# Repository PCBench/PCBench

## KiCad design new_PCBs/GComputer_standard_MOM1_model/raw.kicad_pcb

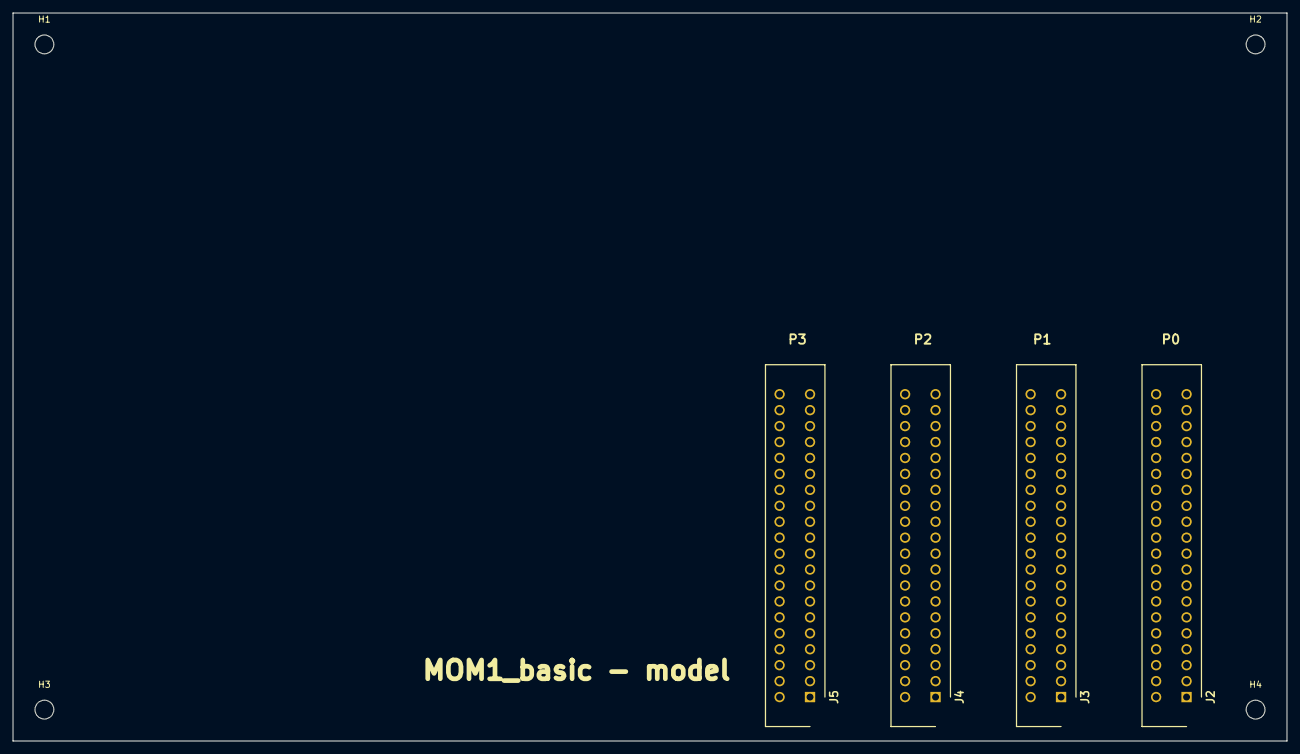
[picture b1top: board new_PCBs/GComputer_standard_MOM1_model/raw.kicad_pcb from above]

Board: 4 copper layers, 203.0 x 116.0 mm, 8 parts (0 on the bottom side), 38 nets, no tracks yet.

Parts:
H1, H2, H3, H4: MountingHole_3mm
J2, J3, J4, J5: PP1_connector_TE_5-5530843-4; TE_5-5530843-4

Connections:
+3V3: J2.39, J3.39, J4.39, J5.39
+5V: J2.40, J3.40, J4.40, J5.40
/BREAD1_0: J2.37, J3.37, J4.37, J5.37
/BREAD1_1: J2.35, J3.35, J4.35, J5.35
/BREAD1_2: J2.33, J3.33, J4.33, J5.33
/BREAD1_3: J2.31, J3.31, J4.31, J5.31
/BREAD1_4: J2.29, J3.29, J4.29, J5.29
/BREAD1_5: J2.27, J3.27, J4.27, J5.27
/BREAD1_6: J2.25, J3.25, J4.25, J5.25
/BREAD1_7: J2.23, J3.23, J4.23, J5.23
/BREAD2_0: J2.21, J3.21, J4.21, J5.21
/BREAD2_1: J2.19, J3.19, J4.19, J5.19
/BREAD2_2: J2.17, J3.17, J4.17, J5.17
/BREAD2_3: J2.15, J3.15, J4.15, J5.15
/BREAD2_4: J2.13, J3.13, J4.13, J5.13
/BREAD2_5: J2.11, J3.11, J4.11, J5.11
/BREAD2_6: J2.9, J3.9, J4.9, J5.9
/BREAD2_7: J2.7, J3.7, J4.7, J5.7
/BWRITE1_0: J2.38, J3.38, J4.38, J5.38
/BWRITE1_1: J2.36, J3.36, J4.36, J5.36
/BWRITE1_2: J2.34, J3.34, J4.34, J5.34
/BWRITE1_3: J2.32, J3.32, J4.32, J5.32
/BWRITE1_4: J2.30, J3.30, J4.30, J5.30
/BWRITE1_5: J2.28, J3.28, J4.28, J5.28
/BWRITE1_6: J2.26, J3.26, J4.26, J5.26
/BWRITE1_7: J2.24, J3.24, J4.24, J5.24
/BWRITE2_0: J2.22, J3.22, J4.22, J5.22
/BWRITE2_1: J2.20, J3.20, J4.20, J5.20
/BWRITE2_2: J2.18, J3.18, J4.18, J5.18
/BWRITE2_3: J2.16, J3.16, J4.16, J5.16
/BWRITE2_4: J2.14, J3.14, J4.14, J5.14
/BWRITE2_5: J2.12, J3.12, J4.12, J5.12
/BWRITE2_6: J2.10, J3.10, J4.10, J5.10
/BWRITE2_7: J2.8, J3.8, J4.8, J5.8
/PERIPHERAL_CLK: J2.3, J3.3, J4.3, J5.3
/SYNC_BIT: J2.6, J3.6, J4.6, J5.6
/~RESET_CLK: J2.5, J3.5, J4.5, J5.5
GND: J2.1, J3.1, J4.1, J5.1

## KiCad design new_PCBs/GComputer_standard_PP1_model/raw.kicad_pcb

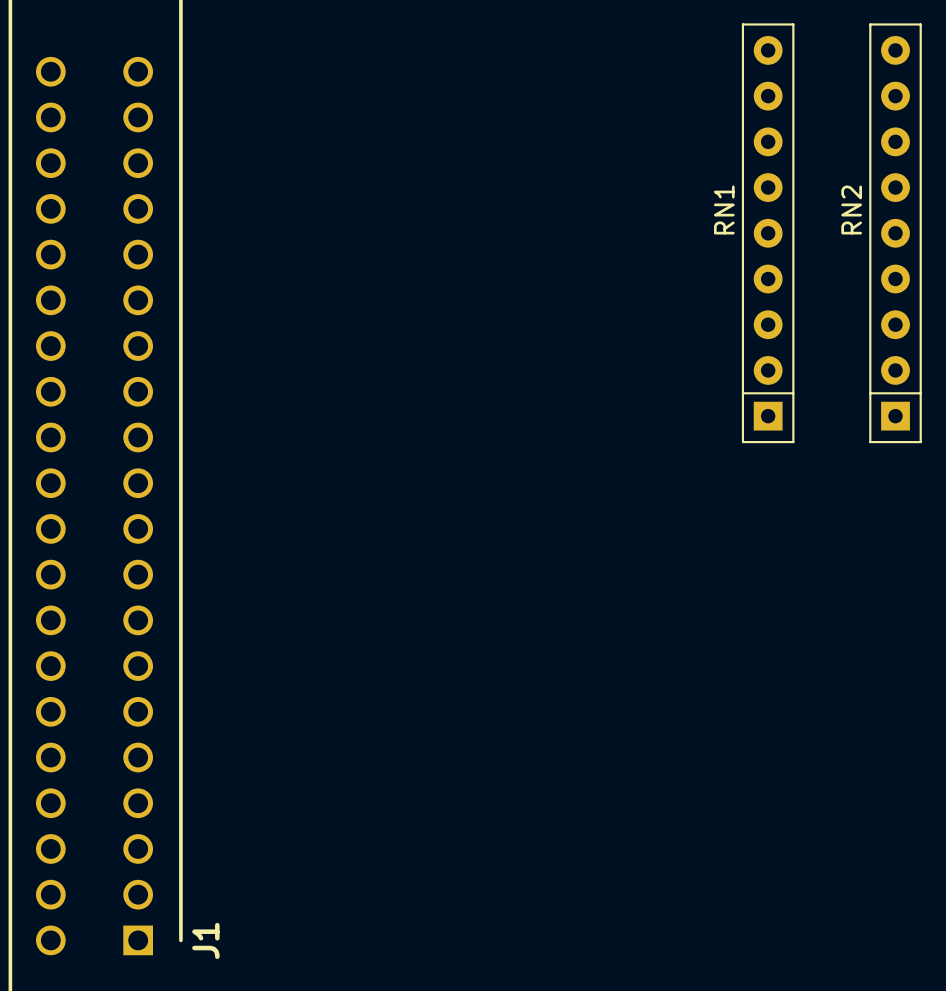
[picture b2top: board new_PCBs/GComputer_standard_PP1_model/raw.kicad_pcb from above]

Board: 4 copper layers, 3 parts (0 on the bottom side), 17 nets, no tracks yet.

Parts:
J1: PP1_receptacle_TE_5-5530843-4; TE_5-5530843-4
RN1, RN2: 8x10k; R_Array_SIP9

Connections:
/BREAD1_0: J1.37, RN1.9
/BREAD1_1: J1.35, RN1.8
/BREAD1_2: J1.33, RN1.7
/BREAD1_3: J1.31, RN1.6
/BREAD1_4: J1.29, RN1.5
/BREAD1_5: J1.27, RN1.4
/BREAD1_6: J1.25, RN1.3
/BREAD1_7: J1.23, RN1.2
/BREAD2_0: J1.21, RN2.9
/BREAD2_1: J1.19, RN2.8
/BREAD2_2: J1.17, RN2.7
/BREAD2_3: J1.15, RN2.6
/BREAD2_4: J1.13, RN2.5
/BREAD2_5: J1.11, RN2.4
/BREAD2_6: J1.9, RN2.3
/BREAD2_7: J1.7, RN2.2
GND: J1.1, RN1.1, RN2.1

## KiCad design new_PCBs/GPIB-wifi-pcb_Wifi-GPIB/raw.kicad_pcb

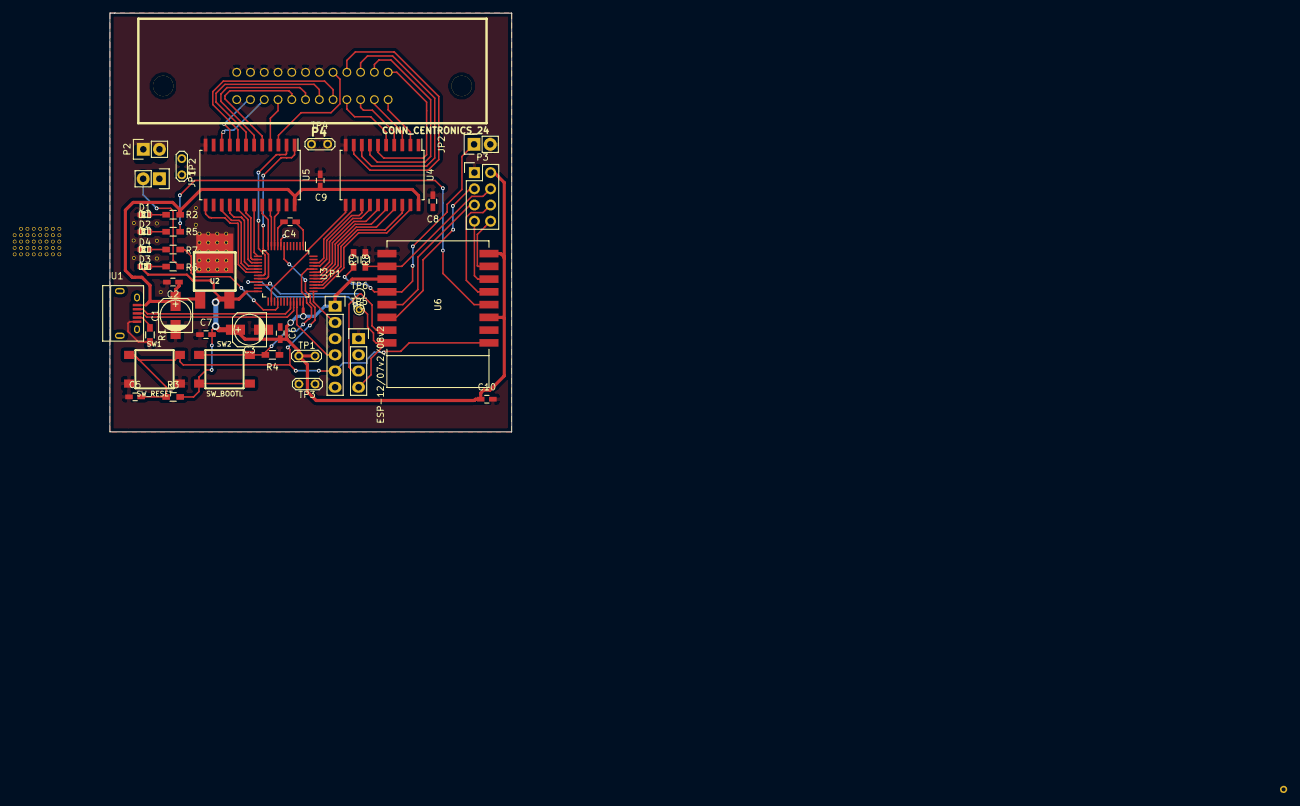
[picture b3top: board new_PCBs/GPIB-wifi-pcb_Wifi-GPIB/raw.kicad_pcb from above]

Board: 2 copper layers, 63.0 x 65.7 mm, 113 parts (0 on the bottom side), 66 nets.

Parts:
C1, C3: 47u; c_elec_5x5.3
C2: 0.33u; C_0603_HandSoldering
C4, C5, C6, C8, C9: 100n; C_0603_HandSoldering
C7: 1u; C_0603_HandSoldering
C10: C; C_0603_HandSoldering
D1: PWR; LED-0603
D2: WIFI; LED-0603
D3: USB; LED-0603
D4: GPIB; LED-0603
GND1, GND2, GND3, GND4, GND5, GND6, GND7, GND8, GND9, GND10, GND11, GND12, GND13, GND14, GND15, GND16, GND17, GND18, GND19, GND20, GND21, GND22, GND23, GND24, GND25, GND26, GND27, GND28, GND29, GND30, GND31, GND32, GND33, GND34, GND35, GND36, GND37, GND38, GND39, GND40, GND41, GND41#2, GND42, GND42#2, GND43, GND43#2, GND44, GND44#2, GND45, GND45#2, GND46, GND46#2, GND47, GND47#2, GND48, GND48#2, GND49, GND50, GND410, GND411, GND412, GND413, GND414, GND415, GND416, GND417, GND418, GND419, GND420: GND; SolderWirePad_single_0-4mmDrill
JP1: USB_LED; Pin_Header_Straight_1x02
JP2: ESP_FLASH_JUMP; Pin_Header_Straight_1x02
P1: SWD; Pin_Header_Straight_1x06
P2: USART; Pin_Header_Straight_1x02
P3: ESP_EXPANSION; Pin_Header_Straight_2x04
P4: CONN_CENTRONICS_24; gpib_conn_male
P5: ESP_PROG; Pin_Header_Straight_1x04
R1: 100k; R_0603_HandSoldering
R2: 270; R_0603_HandSoldering
R3, R4, R5, R6, R7, R8, R9: R; R_0603_HandSoldering
SW1: SW_RESET; SW_PUSH_SMD
SW2: SW_BOOTL; SW_PUSH_SMD
TP1, TP2, TP3, TP4: TESTPOINT
TP5, TP6: TESTPOINT; PINTST
U1: MICRO-B_USB; USB_Micro-B
U2: BA33BC0FP-E2; TO-252
U3: STM32F072CBT6; LQFP-48_7x7mm_Pitch0.5mm
U4: SN75160B; SOIC-20_7.5x12.8mm_Pitch1.27mm
U5: SN75162B; SOIC-24_7.5x15.4mm_Pitch1.27mm
U6: ESP-12/07v2/08v2; ESP-07

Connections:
+3.3V: C3.1, C4.2, C6.2, C7.2, C10.1, D3.1, P1.1, P3.2, P5.2, R3.2, R8.1, SW2.2, TP1.1, U2.3, U3.9, U3.24, U3.36, U3.48, U6.3, U6.8, U6.11
+5V: C1.1, C2.1, C8.1, C9.1, R2.1, TP2.1, U1.1, U2.1, U4.20, U5.24
/GPIB and Cortex M0/ATN: U3.16, U5.16
/GPIB and Cortex M0/D1: U3.38, U4.19
/GPIB and Cortex M0/D2: U3.39, U4.18
/GPIB and Cortex M0/D3: U3.40, U4.17
/GPIB and Cortex M0/D4: U3.41, U4.16
/GPIB and Cortex M0/D5: U3.42, U4.15
/GPIB and Cortex M0/D6: U3.43, U4.14
/GPIB and Cortex M0/D7: U3.45, U4.13
/GPIB and Cortex M0/D8: U3.46, U4.12
/GPIB and Cortex M0/DAV: U3.14, U5.18
/GPIB and Cortex M0/EOI: U3.15, U5.17
/GPIB and Cortex M0/ESP_GPIO_4: P3.3, U6.14
/GPIB and Cortex M0/ESP_GPIO_5: P3.5, U6.13
/GPIB and Cortex M0/ESP_GPIO_12: P3.7, U6.6
/GPIB and Cortex M0/ESP_GPIO_13: P3.8, U6.7
/GPIB and Cortex M0/ESP_GPIO_14: P3.6, U6.5
/GPIB and Cortex M0/ESP_GPIO_15: P3.4, R9.1, U6.10
/GPIB and Cortex M0/ESP_GPIO_16: R5.2, U6.4
/GPIB and Cortex M0/ESP_RXD: P5.3, TP6.1, U3.22, U6.15
/GPIB and Cortex M0/ESP_TXD: P5.4, TP5.1, U3.21, U6.16
/GPIB and Cortex M0/IFC: U3.11, U5.21
/GPIB and Cortex M0/NDAC: U3.12, U5.20
/GPIB and Cortex M0/NRFD: U3.13, U5.19
/GPIB and Cortex M0/REN: U3.10, U5.22
/GPIB and Cortex M0/SRQ: U3.17, U5.15
/GPIB and Cortex M0/USB_D+: U1.3, U3.33
/GPIB and Cortex M0/USB_D-: U1.2, U3.32
BOOT0: R4.2, SW2.1, U3.44
ESP_GPIO0: JP2.1, R8.2, U6.12
GND: C1.2, C2.2, C3.2, C5.1, C6.1, C7.1, C8.2, C9.2, C10.2, D1.2, D2.2, D4.2, GND1.1, GND2.1, GND3.1, GND4.1, GND5.1, GND6.1, GND7.1, GND8.1, GND9.1, GND10.1, GND11.1, GND12.1, GND13.1, GND14.1, GND15.1, GND16.1, GND17.1, GND18.1, GND19.1, GND20.1, GND21.1, GND22.1, GND23.1, GND24.1, GND25.1, GND26.1, GND27.1, GND28.1, GND29.1, GND30.1, GND31.1, GND32.1, GND33.1, GND34.1, GND35.1, GND36.1, GND37.1, GND38.1, GND39.1, GND40.1, GND41.1, GND41#2.1, GND42.1, GND42#2.1, GND43.1, GND43#2.1, GND44.1, GND44#2.1, GND45.1, GND45#2.1, GND46.1, GND46#2.1, GND47.1, GND47#2.1, GND48.1, GND48#2.1, GND49.1, GND50.1, GND410.1, GND411.1, GND412.1, GND413.1, GND414.1, GND415.1, GND416.1, GND417.1, GND418.1, GND419.1, GND420.1, JP2.2, P1.3, P3.1, P4.12, P4.18, P4.19, P4.20, P4.21, P4.22, P4.23, P4.24, P5.1, R1.2, R4.1, R9.2, SW1.2, TP3.1, TP4.1, U1.5, U2.2, U3.8, U3.23, U3.35, U3.47, U4.10, U5.12, U6.9
GPIB_BUS_ATN: P4.11, U5.9
GPIB_BUS_D1: P4.1, U4.2
GPIB_BUS_D2: P4.2, U4.3
GPIB_BUS_D3: P4.3, U4.4
GPIB_BUS_D4: P4.4, U4.5
GPIB_BUS_D5: P4.13, U4.6
GPIB_BUS_D6: P4.14, U4.7
GPIB_BUS_D7: P4.15, U4.8
GPIB_BUS_D8: P4.16, U4.9
GPIB_BUS_DAV: P4.6, U5.7
GPIB_BUS_EOI: P4.5, U5.8
GPIB_BUS_IFC: P4.9, U5.4
GPIB_BUS_NDAC: P4.8, U5.5
GPIB_BUS_NRFD: P4.7, U5.6
GPIB_BUS_REN: P4.17, U5.3
GPIB_BUS_SRQ: P4.10, U5.10
GPIB_CTRL_DC: U3.18, U5.13
GPIB_CTRL_SC: U3.20, U5.1
GPIB_CTRL_TE: U3.19, U5.2
GPIB_DATA_PE: U3.26, U4.11
GPIB_DATA_TE: U3.25, U4.1
GPIB_SEND_LED: R7.2, U3.28
NRST: C5.2, P1.5, R3.1, SW1.1, U3.7, U6.1
unnamed: C4.1, U3.1
unnamed: D1.1, R2.2
unnamed: D2.1, R5.1
unnamed: D3.2, R6.1
unnamed: D4.1, R7.1
unnamed: R1.1, U1.4
SWCLK: P1.2, U3.37
SWDIO: JP1.1, P1.4, U3.34
USART1_RX: P2.2, U3.31
USART1_TX: P2.1, U3.30
USB_NOE: JP1.2, R6.2

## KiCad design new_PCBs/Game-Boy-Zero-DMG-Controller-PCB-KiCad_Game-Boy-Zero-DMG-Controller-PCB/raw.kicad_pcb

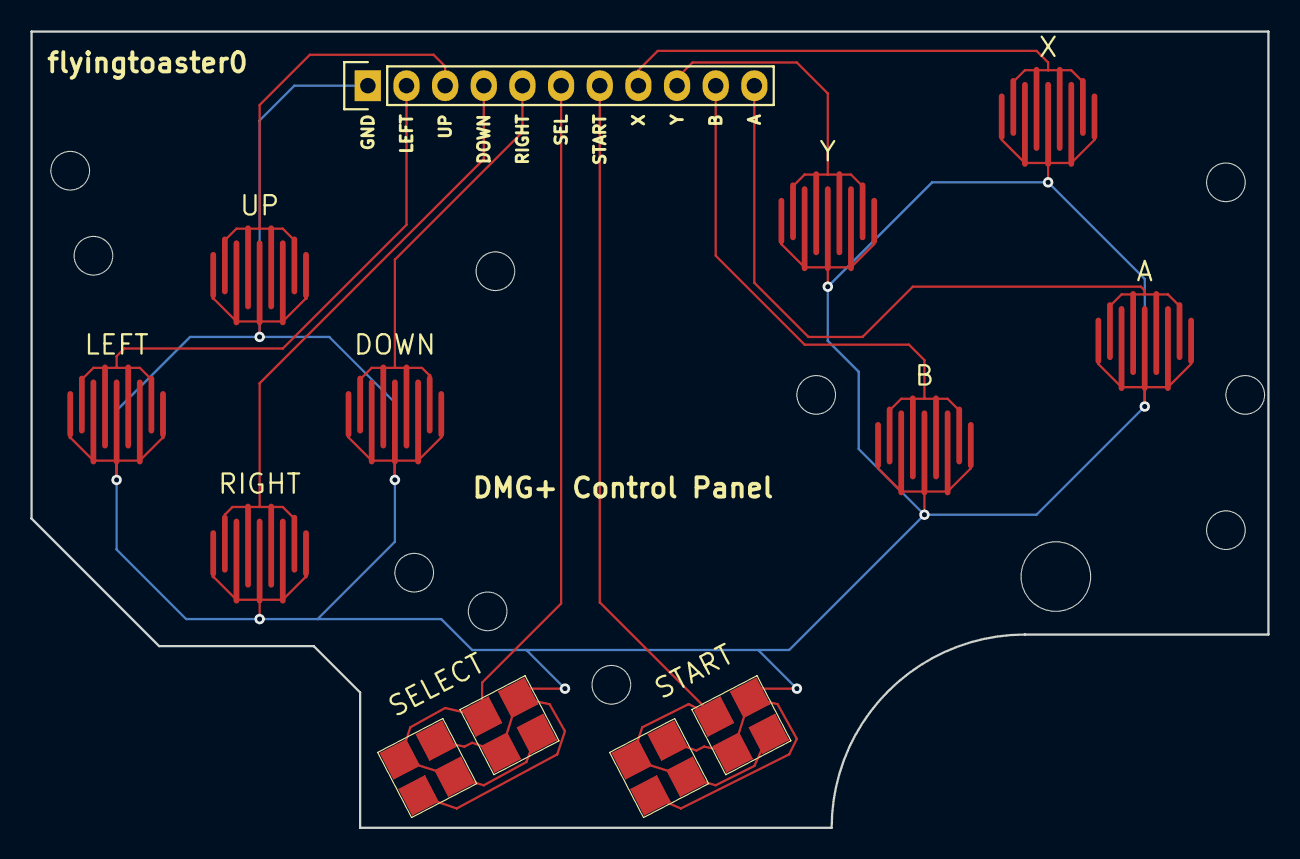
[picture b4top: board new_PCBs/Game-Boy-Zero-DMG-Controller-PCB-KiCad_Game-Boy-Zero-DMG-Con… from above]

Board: 2 copper layers, 81.3 x 52.3 mm, 11 parts (0 on the bottom side), 11 nets.

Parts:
P1: CONN_01X11; Socket_Strip_Straight_1x11
SW1: LEFT; GameBoy-DMG-BTN
SW2: UP; GameBoy-DMG-BTN
SW3: DOWN; GameBoy-DMG-BTN
SW4: RIGHT; GameBoy-DMG-BTN
SW5: SELECT; GameBoy-DMG-START-SEL
SW6: START; GameBoy-DMG-START-SEL
SW7: X; GameBoy-DMG-BTN
SW8: Y; GameBoy-DMG-BTN
SW9: B; GameBoy-DMG-BTN
SW10: A; GameBoy-DMG-BTN

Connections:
GND: P1.1, SW1.1, SW2.1, SW3.1, SW4.1, SW5.1, SW6.1, SW7.1, SW8.1, SW9.1, SW10.1
unnamed: P1.2, SW1.2
unnamed: P1.3, SW2.2
unnamed: P1.4, SW4.2
unnamed: P1.5, SW3.2
unnamed: P1.6, SW5.2
unnamed: P1.7, SW6.2
unnamed: P1.8, SW7.2
unnamed: P1.9, SW8.2
unnamed: P1.10, SW9.2
unnamed: P1.11, SW10.2
